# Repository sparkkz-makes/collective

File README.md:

# collective
Helicopter collective control for flight sim

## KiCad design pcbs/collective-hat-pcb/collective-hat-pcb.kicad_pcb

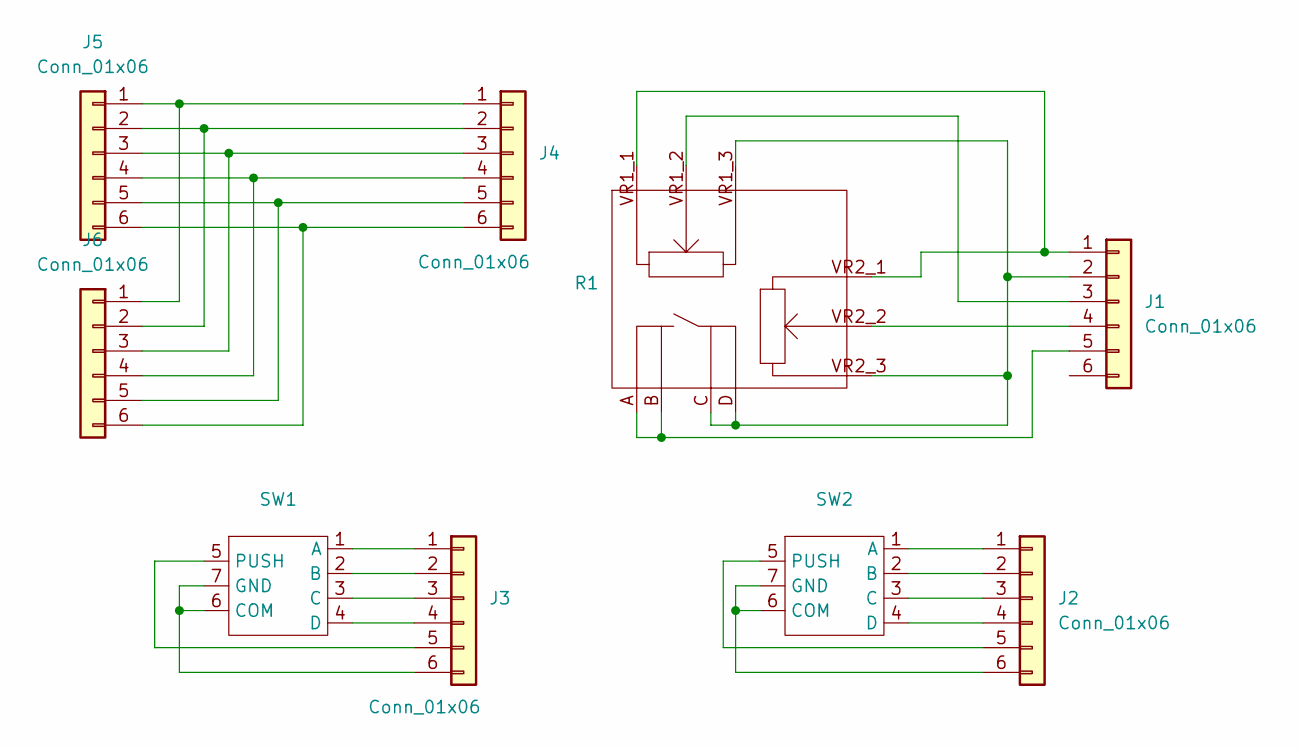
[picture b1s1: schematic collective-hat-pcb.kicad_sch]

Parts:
J1, J2, J3, J4: Conn_01x06; JST_PH_S6B-PH-K_1x06_P2.00mm_Horizontal
J5, J6: Conn_01x06; JST_PH_B6B-PH-K_1x06_P2.00mm_Vertical
R1: CNK_THB001P
SW1, SW2: hat-switch

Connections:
unnamed: J1.1, R1.VR1_1, R1.VR2_1
unnamed: J1.2, R1.C, R1.D, R1.VR1_3, R1.VR2_3
unnamed: J1.3, R1.VR1_2
unnamed: J1.4, R1.VR2_2
unnamed: J1.5, R1.A, R1.B
unnamed: J2.1, SW2.1 (A)
unnamed: J2.2, SW2.2 (B)
unnamed: J2.3, SW2.3 (C)
unnamed: J2.4, SW2.4 (D)
unnamed: J2.5, SW2.5 (PUSH)
unnamed: J2.6, SW2.6 (COM), SW2.7 (GND)
unnamed: J3.1, SW1.1 (A)
unnamed: J3.2, SW1.2 (B)
unnamed: J3.3, SW1.3 (C)
unnamed: J3.4, SW1.4 (D)
unnamed: J3.5, SW1.5 (PUSH)
unnamed: J3.6, SW1.6 (COM), SW1.7 (GND)
unnamed: J4.1, J5.1, J6.1
unnamed: J4.2, J5.2, J6.2
unnamed: J4.3, J5.3, J6.3
unnamed: J4.4, J5.4, J6.4
unnamed: J4.5, J5.5, J6.5
unnamed: J4.6, J5.6, J6.6

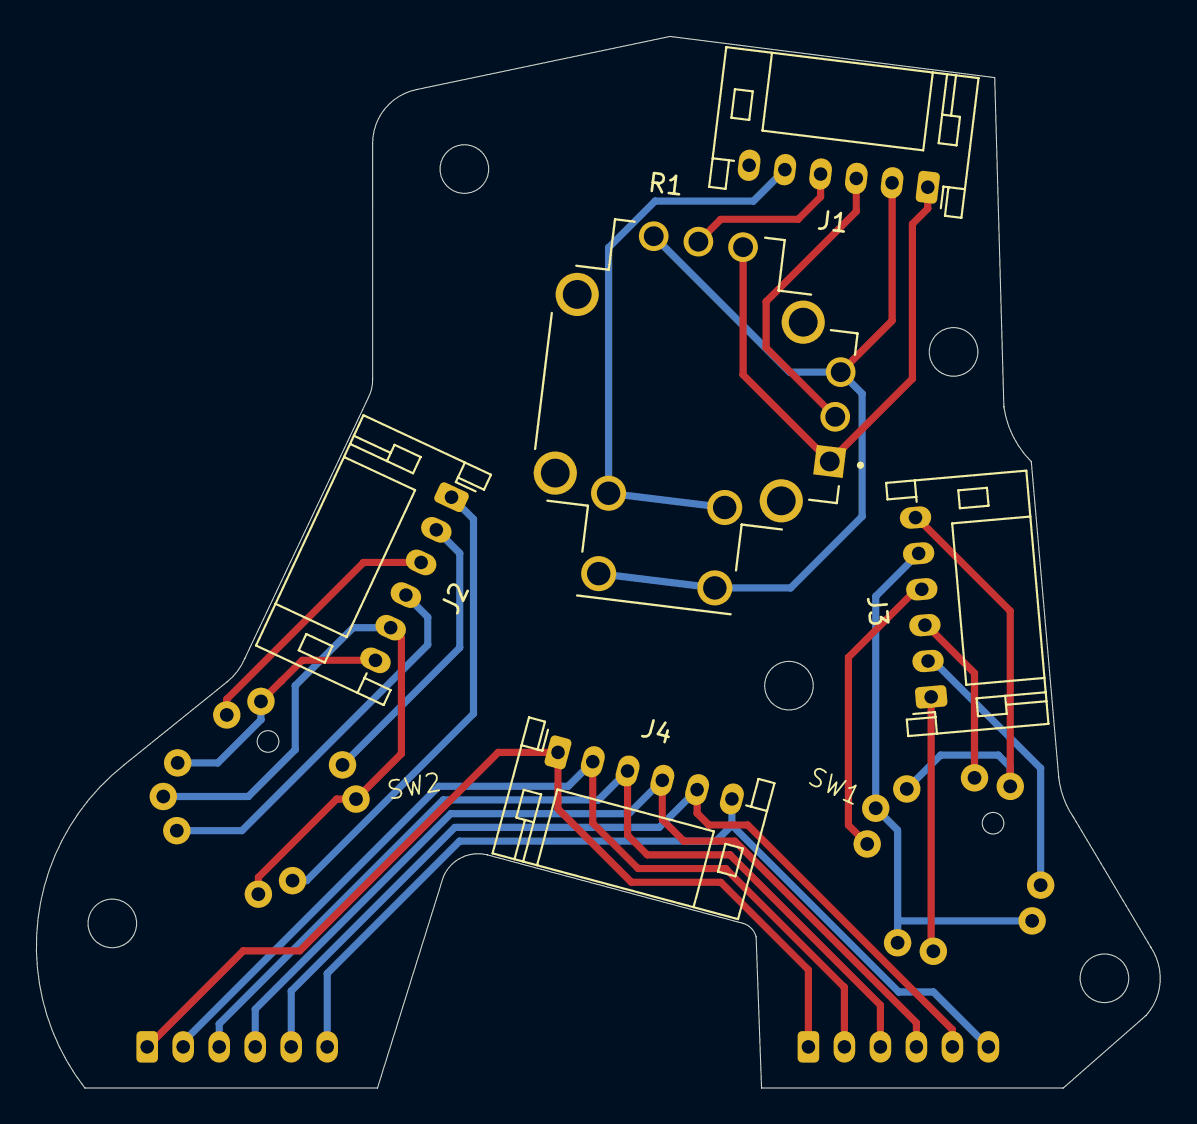
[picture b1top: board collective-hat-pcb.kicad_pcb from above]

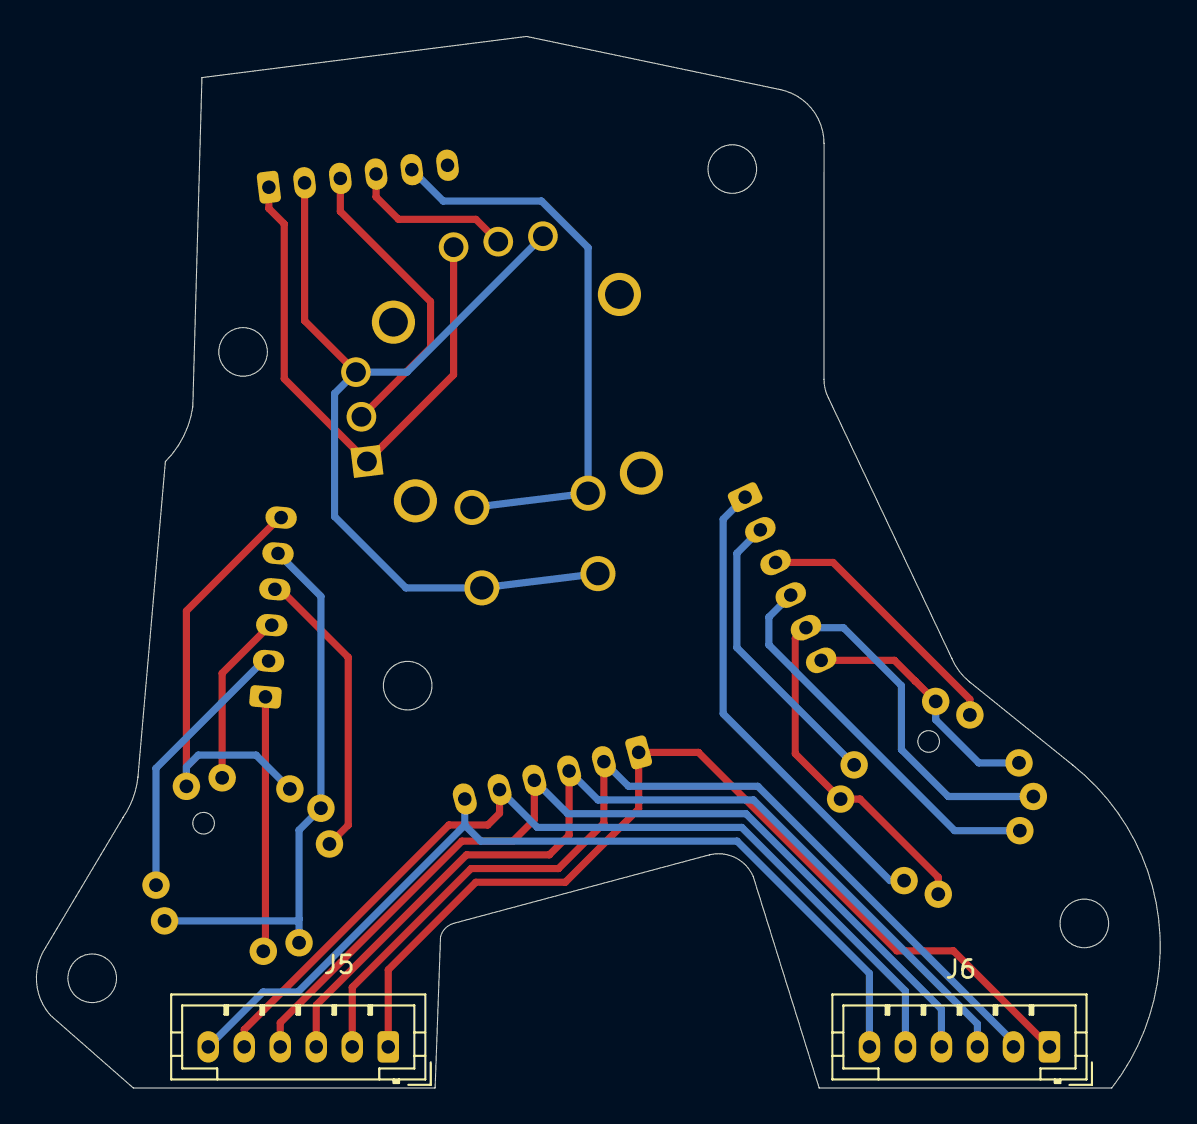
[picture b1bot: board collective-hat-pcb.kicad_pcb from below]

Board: 2 copper layers, 62.4 x 58.4 mm, 9 parts (2 on the bottom side), 23 nets.

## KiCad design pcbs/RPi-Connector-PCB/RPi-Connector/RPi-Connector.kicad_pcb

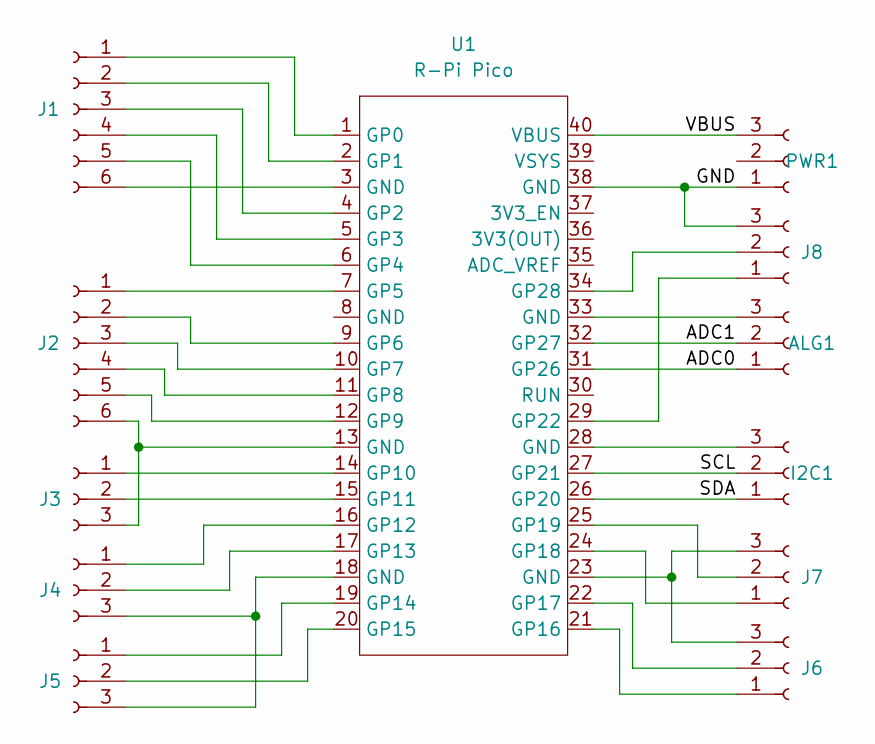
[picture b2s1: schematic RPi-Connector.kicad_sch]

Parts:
ALG1: Conn_01x03_Socket; JST_PH_B3B-PH-K_1x03_P2.00mm_Vertical
I2C1: Conn_01x03_Socket; JST_PH_B3B-PH-K_1x03_P2.00mm_Vertical
J1, J2: Conn_01x06_Socket; JST_PH_B6B-PH-K_1x06_P2.00mm_Vertical
J3, J4, J5, J6, J7, J8: Conn_01x03_Socket; JST_PH_B3B-PH-K_1x03_P2.00mm_Vertical
PWR1: Conn_01x03_Socket; JST_PH_B3B-PH-K_1x03_P2.00mm_Vertical
U1: R-Pi Pico; DIP-40_700_ELL

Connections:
/ADC0: ALG1.1, U1.31 (GP26)
/ADC1: ALG1.2, U1.32 (GP27)
/GND: J8.3, PWR1.1, U1.38 (GND)
/SCL: I2C1.2, U1.27 (GP21)
/SDA: I2C1.1, U1.26 (GP20)
/VBUS: PWR1.3, U1.40 (VBUS)
unnamed: ALG1.3, U1.33 (GND)
unnamed: I2C1.3, U1.28 (GND)
unnamed: J1.1, U1.1 (GP0)
unnamed: J1.2, U1.2 (GP1)
unnamed: J1.3, U1.4 (GP2)
unnamed: J1.4, U1.5 (GP3)
unnamed: J1.5, U1.6 (GP4)
unnamed: J1.6, U1.3 (GND)
unnamed: J2.1, U1.7 (GP5)
unnamed: J2.2, U1.9 (GP6)
unnamed: J2.3, U1.10 (GP7)
unnamed: J2.4, U1.11 (GP8)
unnamed: J2.5, U1.12 (GP9)
unnamed: J2.6, J3.3, U1.13 (GND)
unnamed: J3.1, U1.14 (GP10)
unnamed: J3.2, U1.15 (GP11)
unnamed: J4.1, U1.16 (GP12)
unnamed: J4.2, U1.17 (GP13)
unnamed: J4.3, J5.3, U1.18 (GND)
unnamed: J5.1, U1.19 (GP14)
unnamed: J5.2, U1.20 (GP15)
unnamed: J6.1, U1.21 (GP16)
unnamed: J6.2, U1.22 (GP17)
unnamed: J6.3, J7.3, U1.23 (GND)
unnamed: J7.1, U1.24 (GP18)
unnamed: J7.2, U1.25 (GP19)
unnamed: J8.1, U1.29 (GP22)
unnamed: J8.2, U1.34 (GP28)

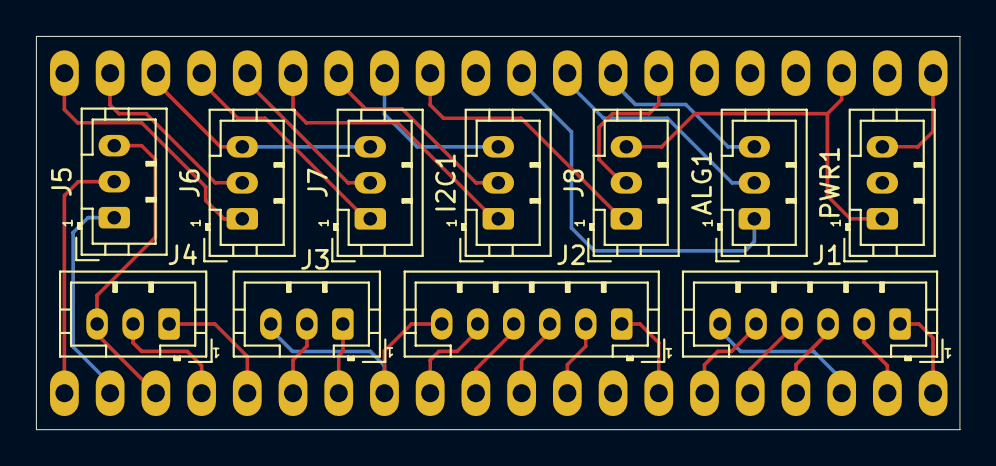
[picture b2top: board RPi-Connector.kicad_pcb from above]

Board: 2 copper layers, 51.3 x 21.8 mm, 12 parts (1 on the bottom side), 34 nets.

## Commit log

2024-05-20 initial upload
2024-05-20 gitignore
2024-05-20 adding doc stuff
2024-05-20 add intro
2024-05-20 move folder
2024-05-21 added pcb drawings
2024-05-24 added new trigger prints and moved old prints
2024-05-27 io board functional, pre core change
2024-05-31 pi code files
2025-04-19 adding doc files
2025-04-22 using as5600
